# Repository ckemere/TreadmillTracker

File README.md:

# Raspberry pi based interface for a rodent treadmill

  - MSP430 based HW data acquisition "hat"
  - Rotational angle tracking using the CUI AMT 102/3 quadrature encoders
  - 1 kHz master clock for timestamping 8 IO lines

## Setup overview

### PiHat
The custom Raspberry Pi hat contains several useful features.
- **Eight GPIO pins** can be used for either receiving or sending signals.
- **Encoder data (AMT102)** is received through the six pins at the top of the board.  
- **2 kHz master clock (DSC6083)** reliably timestamps input data.
- **Button** ?
- **MSP430 microcontroller** packages and sends serial messages containing timestamped data every 2 ms. Programmed via seven pins at bottom of board.
- **Shield** interfaces with Raspberry Pi pins, including the eight GPIO pins connected to RaspPi GPIO pins.

### Accessories
#### Rotary encoder
The AMT102 sends signals in increments with resolution of 4096 steps/revolution. Thus each pulse signals that the wheel has turned 1/4096 of a revolution. For more details, look at the specs in the data sheet contained in *Firmware*.

#### Lick sensor
The lick sensor sends digital signals to one of the Hat's GPIO pins to indicate a licking event is occurring. More details in lick-sensor repository.

#### Nose-poke sensor
The nose-poke sensor sends digital signals to one of the Hat's GPIO pins to indicate a nose-poke event is occurring.

#### Syringe pump
The syringe pump receives 5V pulses from a GPIO pin on the Hat to dispense liquid rewards. The duration of the pulse determines the volume of reward dispensed (given a syringe diameter and pump speed).

#### Sound card
The sound card converts the digital audio file (.wav) to an analog signal to drive the external speakers. It can either be integrated with the host computer (if using a desktop), or as a shield (if using a Raspberry Pi; the HiFiBerry Amp2, for example, uses built-in drivers in the Raspberry Pi Linux kernel to obtain high-quality I2C digital audio from the GPIO pins, which it converts to an analog signal for speaker input. See [here](https://www.hifiberry.com/build/documentation/configuring-linux-3-18-x/) for more details.)

#### Breakout board
In order to streamline I/O connections between the custom hat and accessories, a custom breakout board shield connects GPIO pins to the rings of 3.5 mm audio jacks. Additionally, the hat Vdd (3.6 V) can be routed to supply voltage to the tips of the audio jacks. With this setup, audio cables can transmit GPIO signal to input and from output devices listed above. For example, audio cables can carry lick and nose-poke sensor digital signals, or send dispense signals to the syringe pumps.

### Host computer
The host computer can either be a Raspberry Pi or a desktop computer. If using a Raspberry Pi, then the custom hat and sound card shield can be stacked on top of one another to form a three-layer, stand-alone device. Otherwise, the host computer is connected to the custom hat via USB, and the native desktop sound card is used to drive the external speakers. In either case, the following components must be installed on the computer.

#### Mixer
The combination of the JACK Audio Connection Kit and minimixer allows for cross-talk between audio sources to function as a software mixer for different audio signals. The JACK daemon runs in the background as a sound server, built on top of the Advanced Linux Sound Architecture (ALSA), for a particular output device (sound card). In a separate process, the minimixer receives different audio feeds in its virtual channels, and controls each sound level of each channel that it feeds into the JACK daemon based on OSC commands it receives. Thus the user has control to dynamically change the output levels of different virtual channels in the minimixer.

#### OSC interface
The mixer, in turn, is interfaced through an OSC package, such `oscpy` in Python, that binds and sends OSC commands to the same port as the mixer. The commands direct the mixer to increase or decrease the gain for each channel in the mixer.

#### Control script
The control script must manage I/O from all the above components, including:
- Processing **behavior input** from the custom hat to determine the current behavior state. The input messages via the serial interface include current time, wheel encoder position, and GPIO values.
- Controlling **audio output** by launching appropriate audio subprocesses (e.g. daemon, mixer) and sending OSC commands to the mixer based on the current behavior state.
- Controlling **behavior output** by sending dispense pulses to the GPIOs associated with syringe pumps based on the current behavior state.

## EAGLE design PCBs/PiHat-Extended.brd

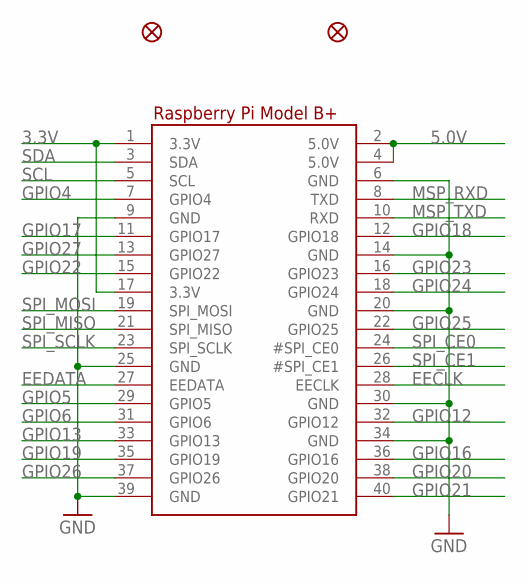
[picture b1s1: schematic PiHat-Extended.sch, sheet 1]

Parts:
FID2, FID3: MICROBUILDER_FIDUCIAL""; MICROBUILDER_FIDUCIAL_1MM
RPI1: MICROBUILDER_RASPBERRYPI_BPLUS_HATNOSLOTS; MICROBUILDER_PI_HAT_NOSLOTS

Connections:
3.3V: RPI1.1 (3.3V), RPI1.17 (3.3V)
5.0V: RPI1.2 (5.0V), RPI1.4 (5.0V); also elsewhere on the board
EECLK: RPI1.28 (EECLK)
EEDATA: RPI1.27 (EEDATA)
GND: RPI1.6 (GND), RPI1.9 (GND), RPI1.14 (GND), RPI1.20 (GND), RPI1.25 (GND), RPI1.30 (GND), RPI1.34 (GND), RPI1.39 (GND); also elsewhere on the board
GPIO4: RPI1.7 (GPIO4)
GPIO5: RPI1.29 (GPIO5); also elsewhere on the board
GPIO6: RPI1.31 (GPIO6); also elsewhere on the board
GPIO12: RPI1.32 (GPIO12)
GPIO13: RPI1.33 (GPIO13)
GPIO16: RPI1.36 (GPIO16); also elsewhere on the board
GPIO17: RPI1.11 (GPIO17); also elsewhere on the board
GPIO18: RPI1.12 (GPIO18)
GPIO19: RPI1.35 (GPIO19)
GPIO20: RPI1.38 (GPIO20)
GPIO21: RPI1.40 (GPIO21)
GPIO22: RPI1.15 (GPIO22); also elsewhere on the board
GPIO23: RPI1.16 (GPIO23); also elsewhere on the board
GPIO24: RPI1.18 (GPIO24); also elsewhere on the board
GPIO25: RPI1.22 (GPIO25); also elsewhere on the board
GPIO26: RPI1.37 (GPIO26); also elsewhere on the board
GPIO27: RPI1.13 (GPIO27); also elsewhere on the board
MSP_RXD: RPI1.8 (TXD); also elsewhere on the board
MSP_TXD: RPI1.10 (RXD); also elsewhere on the board
SCL: RPI1.5 (SCL)
SDA: RPI1.3 (SDA)
SPI_CE0: RPI1.24 (#SPI_CE0)
SPI_CE1: RPI1.26 (#SPI_CE1)
SPI_MISO: RPI1.21 (SPI_MISO)
SPI_MOSI: RPI1.19 (SPI_MOSI)
SPI_SCLK: RPI1.23 (SPI_SCLK)

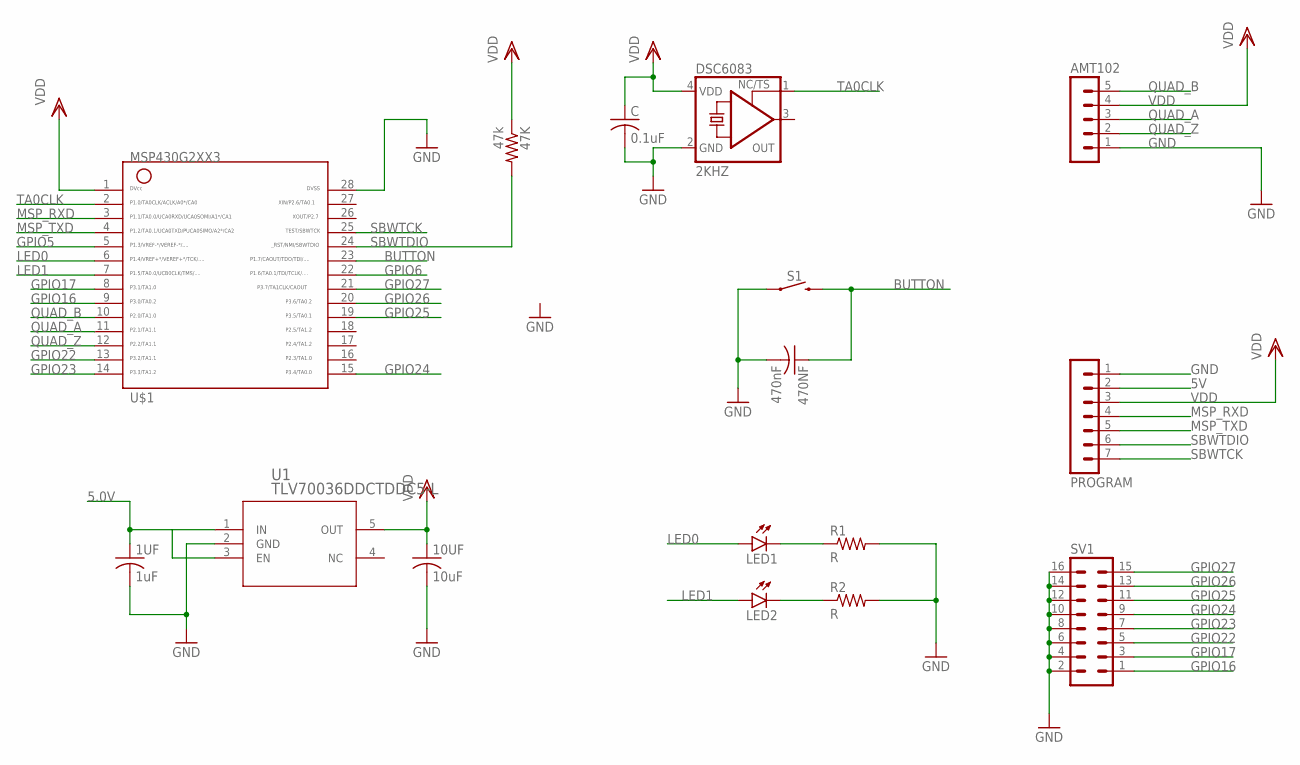
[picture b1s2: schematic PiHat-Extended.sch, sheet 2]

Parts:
1UF: 1uF; C0603
10UF: 10uF; C1206
47K: 47k; R0603
470NF: 470nF; C0603
AMT102: MA05-1
C: 0.1uF; C0603
DSC6083: 2KHZ; 3.2X2.5_KXO-V96
LED1, LED2: LEDCHIPLED_1206; CHIPLED_1206
PROGRAM: MA07-1
R1, R2: R; R0603
S1: MOMENTARY-SWITCH-SPST-PTH-6.0MM; TACTILE_SWITCH_PTH_6.0MM
SV1: MA08-2
U1: TLV70036DDCTDDC5-L; DDC5-L
U$1: MSP430; PW28

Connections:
5.0V: 1UF.1, U1.1 (IN), U1.3 (EN); also elsewhere on the board
5V: PROGRAM.2
BUTTON: 470NF.1, S1.3 (2), U$1.23
GND: 1UF.2, 10UF.2, 470NF.2, AMT102.1, C.2, DSC6083.2 (GND), PROGRAM.1, R1.2, R2.2, S1.1, SV1.2, SV1.4, SV1.6, SV1.8, SV1.10, SV1.12, SV1.14, SV1.16, U1.2 (GND), U$1.28; also elsewhere on the board
GPIO5: U$1.5; also elsewhere on the board
GPIO6: U$1.22; also elsewhere on the board
GPIO16: SV1.1, U$1.9; also elsewhere on the board
GPIO17: SV1.3, U$1.8; also elsewhere on the board
GPIO22: SV1.5, U$1.13; also elsewhere on the board
GPIO23: SV1.7, U$1.14; also elsewhere on the board
GPIO24: SV1.9, U$1.15; also elsewhere on the board
GPIO25: SV1.11, U$1.19; also elsewhere on the board
GPIO26: SV1.13, U$1.20; also elsewhere on the board
GPIO27: SV1.15, U$1.21; also elsewhere on the board
LED0: LED1.A, U$1.6
LED1: LED2.A, U$1.7
MSP_RXD: PROGRAM.4, U$1.3; also elsewhere on the board
MSP_TXD: PROGRAM.5, U$1.4; also elsewhere on the board
unnamed: LED1.C, R1.1
unnamed: LED2.C, R2.1
QUAD_A: AMT102.3, U$1.11
QUAD_B: AMT102.5, U$1.10
QUAD_Z: AMT102.2, U$1.12
SBWTCK: PROGRAM.7, U$1.25
SBWTDIO: 47K.2, PROGRAM.6, U$1.24
TA0CLK: DSC6083.1 (TS), U$1.2
VDD: 10UF.1, 47K.1, AMT102.4, C.1, DSC6083.4 (VDD), PROGRAM.3, U1.5 (OUT), U$1.1; also elsewhere on the board

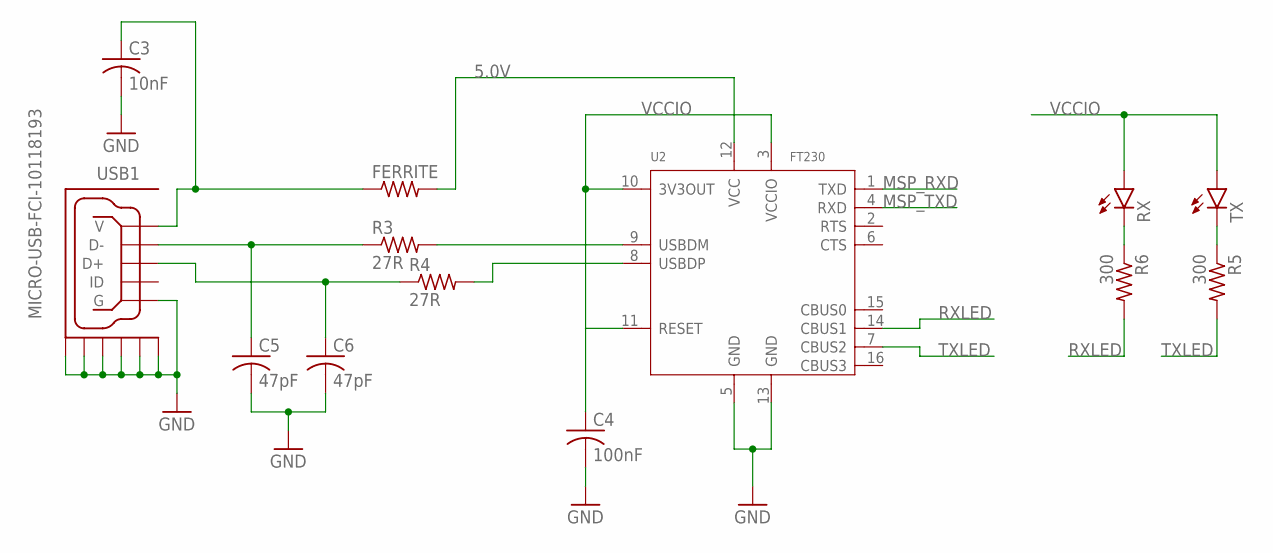
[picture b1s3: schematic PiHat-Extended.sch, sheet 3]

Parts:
C3: 10nF; C0603
C4: 100nF; C0603
C5, C6: 47pF; C0603
FERRITE: R-US_R0805; R0805
R3, R4: 27R; R0603
R5, R6: 300; R0603
RX: LEDCHIPLED_1206; CHIPLED_1206
TX: LEDCHIPLED_1206; CHIPLED_1206
U2: FT230; SSOP16-0.635-5X4MM
USB1: MICRO-USB-FCI-10118193; FCI-10118193-0001LF

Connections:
5.0V: FERRITE.2, U2.12 (VCC); also elsewhere on the board
GND: C3.2, C4.2, C5.2, C6.2, U2.5 (GND), U2.13 (GND), USB1.5 (G), USB1.G1 (GND1), USB1.G2 (GND2), USB1.G3 (GND3), USB1.G4 (GND4), USB1.G5 (GND5), USB1.G6 (GND6); also elsewhere on the board
MSP_RXD: U2.1 (TXD); also elsewhere on the board
MSP_TXD: U2.4 (RXD); also elsewhere on the board
unnamed: C3.1, FERRITE.1, USB1.1 (V)
unnamed: C5.1, R3.1, USB1.2 (D-)
unnamed: R3.2, U2.9 (USBDM)
unnamed: C6.1, R4.1, USB1.3 (D+)
unnamed: R4.2, U2.8 (USBDP)
unnamed: R6.1, RX.C
unnamed: R5.1, TX.C
RXLED: R6.2, U2.14 (CBUS1)
TXLED: R5.2, U2.7 (CBUS2)
VCCIO: C4.1, RX.A, TX.A, U2.3 (VCCIO), U2.10 (3V3OUT), U2.11 (RESET)

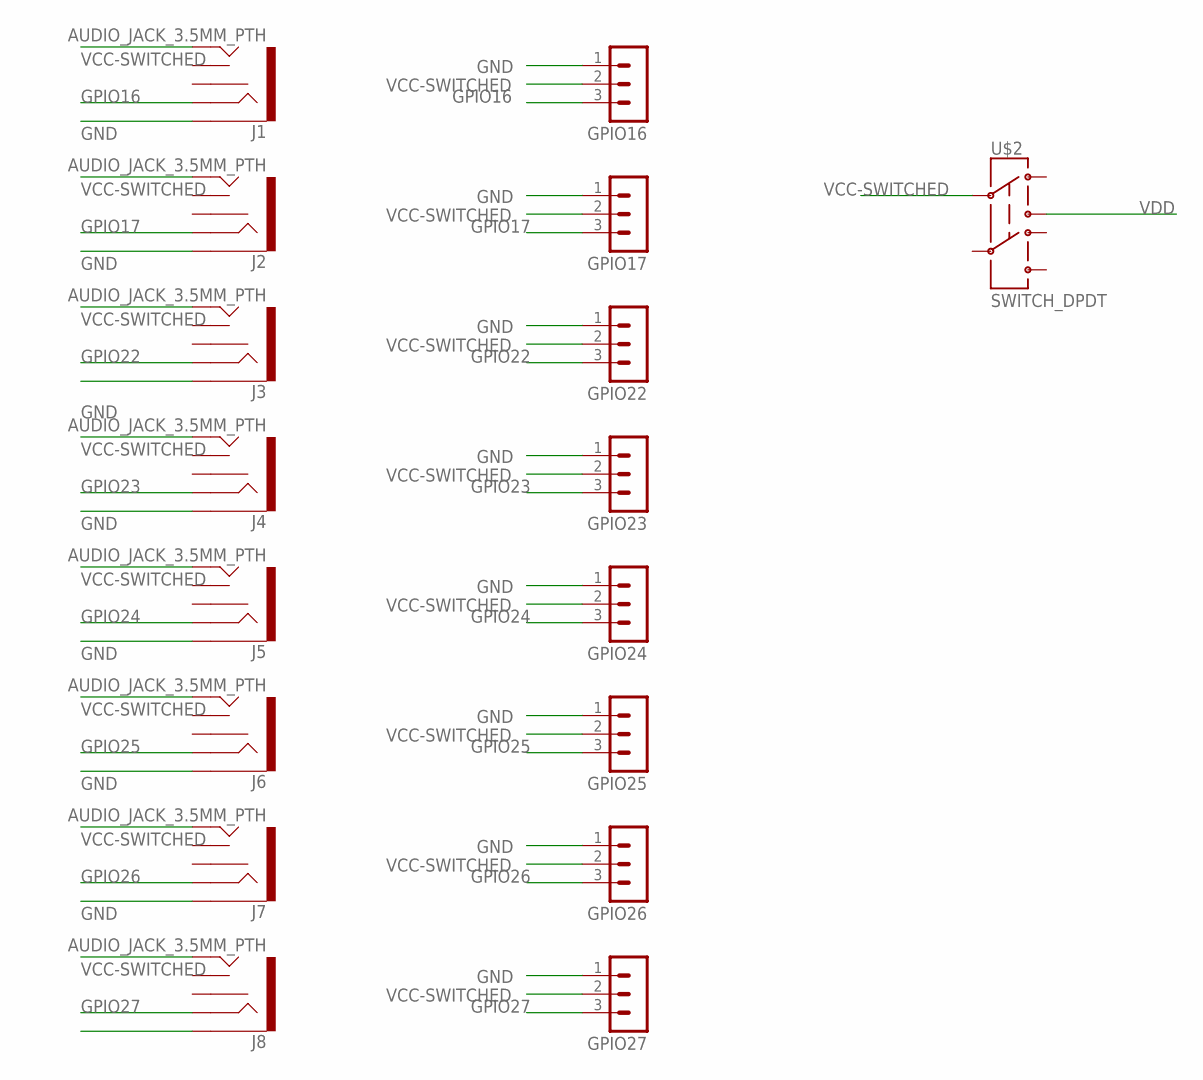
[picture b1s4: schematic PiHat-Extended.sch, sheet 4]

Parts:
GPIO16, GPIO17, GPIO22, GPIO23, GPIO24, GPIO25, GPIO26, GPIO27: MA03-1
J1, J2, J3, J4, J5, J6, J7, J8: AUDIO_JACK_3.5MM_PTH; AUDIO-JACK
U$2: SWITCH_DPDT; JS_DPDT_TH

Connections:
GND: GPIO16.1, GPIO17.1, GPIO22.1, GPIO23.1, GPIO24.1, GPIO25.1, GPIO26.1, GPIO27.1, J1.SLEEVE, J2.SLEEVE, J3.SLEEVE, J4.SLEEVE, J5.SLEEVE, J6.SLEEVE, J7.SLEEVE, J8.SLEEVE; also elsewhere on the board
GPIO16: GPIO16.3, J1.RING; also elsewhere on the board
GPIO17: GPIO17.3, J2.RING; also elsewhere on the board
GPIO22: GPIO22.3, J3.RING; also elsewhere on the board
GPIO23: GPIO23.3, J4.RING; also elsewhere on the board
GPIO24: GPIO24.3, J5.RING; also elsewhere on the board
GPIO25: GPIO25.3, J6.RING; also elsewhere on the board
GPIO26: GPIO26.3, J7.RING; also elsewhere on the board
GPIO27: GPIO27.3, J8.RING; also elsewhere on the board
VCC-SWITCHED: GPIO16.2, GPIO17.2, GPIO22.2, GPIO23.2, GPIO24.2, GPIO25.2, GPIO26.2, GPIO27.2, J1.TIP, J2.TIP, J3.TIP, J4.TIP, J5.TIP, J6.TIP, J7.TIP, J8.TIP, U$2.2
VDD: U$2.3; also elsewhere on the board

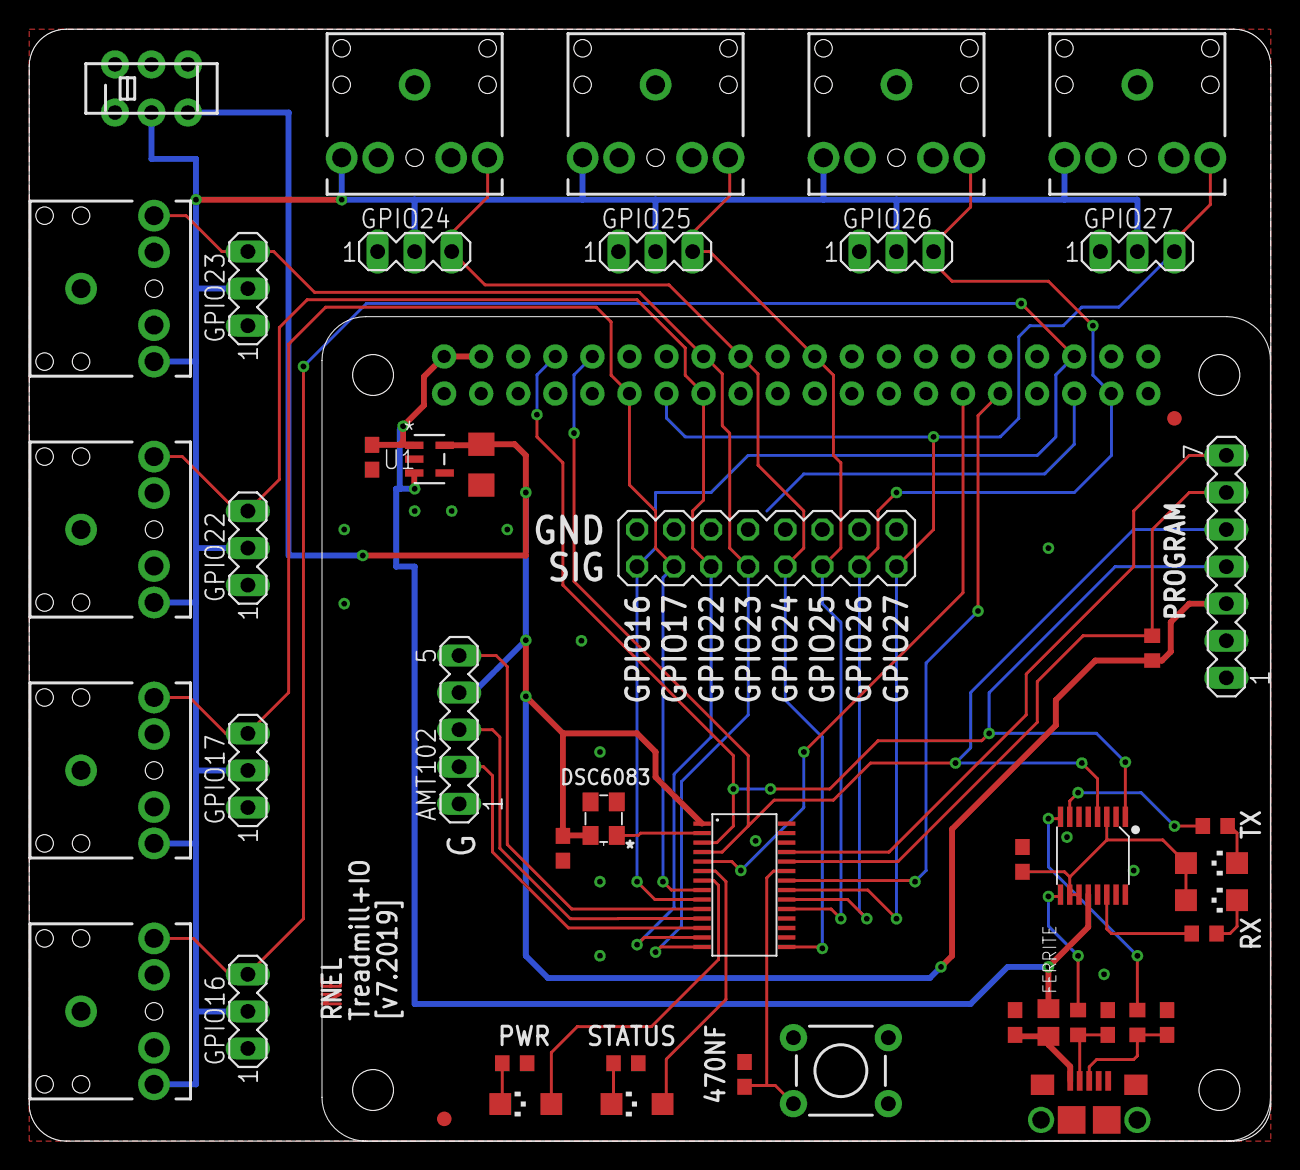
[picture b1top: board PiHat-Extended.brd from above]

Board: 2 copper layers, 85.1 x 76.2 mm, 49 parts (0 on the bottom side), 38 nets.

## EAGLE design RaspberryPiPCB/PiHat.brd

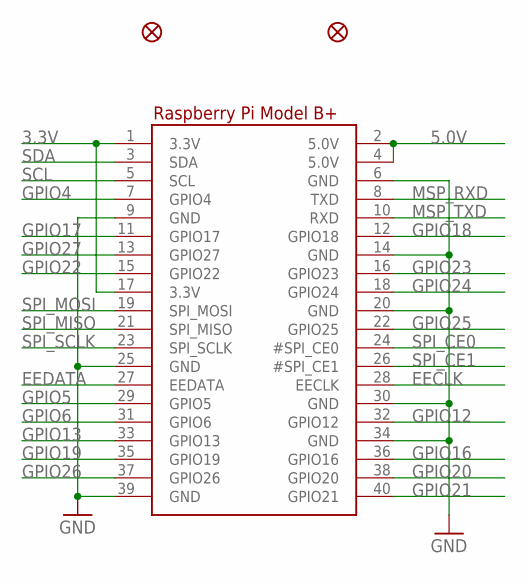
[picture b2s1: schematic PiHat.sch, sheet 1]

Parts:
FID2, FID3: FIDUCIAL""; FIDUCIAL_1MM
RPI1: RASPBERRYPI_BPLUS_HATNOSLOTS; PI_HAT_NOSLOTS

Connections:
3.3V: RPI1.1 (3.3V), RPI1.17 (3.3V)
5.0V: RPI1.2 (5.0V), RPI1.4 (5.0V); also elsewhere on the board
EECLK: RPI1.28 (EECLK)
EEDATA: RPI1.27 (EEDATA)
GND: RPI1.6 (GND), RPI1.9 (GND), RPI1.14 (GND), RPI1.20 (GND), RPI1.25 (GND), RPI1.30 (GND), RPI1.34 (GND), RPI1.39 (GND); also elsewhere on the board
GPIO4: RPI1.7 (GPIO4)
GPIO5: RPI1.29 (GPIO5); also elsewhere on the board
GPIO6: RPI1.31 (GPIO6); also elsewhere on the board
GPIO12: RPI1.32 (GPIO12)
GPIO13: RPI1.33 (GPIO13)
GPIO16: RPI1.36 (GPIO16); also elsewhere on the board
GPIO17: RPI1.11 (GPIO17); also elsewhere on the board
GPIO18: RPI1.12 (GPIO18); also elsewhere on the board
GPIO19: RPI1.35 (GPIO19); also elsewhere on the board
GPIO20: RPI1.38 (GPIO20)
GPIO21: RPI1.40 (GPIO21)
GPIO22: RPI1.15 (GPIO22)
GPIO23: RPI1.16 (GPIO23)
GPIO24: RPI1.18 (GPIO24); also elsewhere on the board
GPIO25: RPI1.22 (GPIO25); also elsewhere on the board
GPIO26: RPI1.37 (GPIO26); also elsewhere on the board
GPIO27: RPI1.13 (GPIO27); also elsewhere on the board
MSP_RXD: RPI1.8 (TXD); also elsewhere on the board
MSP_TXD: RPI1.10 (RXD); also elsewhere on the board
SCL: RPI1.5 (SCL)
SDA: RPI1.3 (SDA)
SPI_CE0: RPI1.24 (#SPI_CE0)
SPI_CE1: RPI1.26 (#SPI_CE1)
SPI_MISO: RPI1.21 (SPI_MISO)
SPI_MOSI: RPI1.19 (SPI_MOSI)
SPI_SCLK: RPI1.23 (SPI_SCLK)

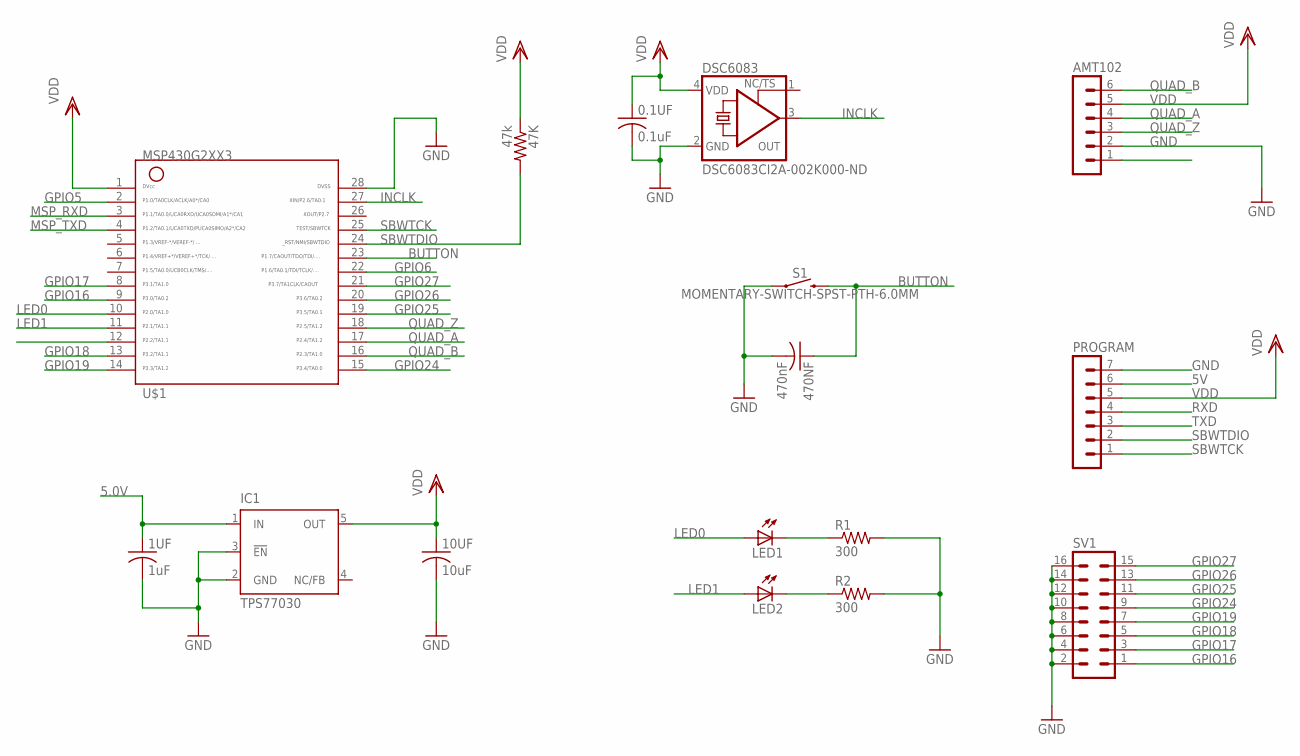
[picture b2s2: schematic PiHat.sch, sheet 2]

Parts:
0.1UF: 0.1uF; C0603
1UF: 1uF; C0603
10UF: 10uF; C1206
47K: 47k; R0603
470NF: 470nF; C0603
AMT102: MA06-1
DSC6083: DSC6083CI2A-002K000-ND; 3.2X2.5_KXO-V96
IC1: TPS77030; SOT23-DBV
LED1, LED2: LEDCHIPLED_1206; CHIPLED_1206
PROGRAM: MA07-1
R1, R2: 300; R0603
S1: MOMENTARY-SWITCH-SPST-PTH-6.0MM; TACTILE_SWITCH_PTH_6.0MM
SV1: MA08-2
U$1: G2XX3---PW28; PW28

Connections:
5.0V: 1UF.1, IC1.1 (IN); also elsewhere on the board
5V: PROGRAM.6
BUTTON: 470NF.1, S1.3 (2), U$1.23
GND: 0.1UF.2, 1UF.2, 10UF.2, 470NF.2, AMT102.2, DSC6083.2 (GND), IC1.2 (GND), IC1.3 (!EN), PROGRAM.7, R1.2, R2.2, S1.1, SV1.2, SV1.4, SV1.6, SV1.8, SV1.10, SV1.12, SV1.14, SV1.16, U$1.28; also elsewhere on the board
GPIO5: U$1.2; also elsewhere on the board
GPIO6: U$1.22; also elsewhere on the board
GPIO16: SV1.1, U$1.9; also elsewhere on the board
GPIO17: SV1.3, U$1.8; also elsewhere on the board
GPIO18: SV1.5, U$1.13; also elsewhere on the board
GPIO19: SV1.7, U$1.14; also elsewhere on the board
GPIO24: SV1.9, U$1.15; also elsewhere on the board
GPIO25: SV1.11, U$1.19; also elsewhere on the board
GPIO26: SV1.13, U$1.20; also elsewhere on the board
GPIO27: SV1.15, U$1.21; also elsewhere on the board
INCLK: DSC6083.3 (OUT), U$1.27
LED0: LED1.A, U$1.10
LED1: LED2.A, U$1.11
MSP_RXD: U$1.3; also elsewhere on the board
MSP_TXD: U$1.4; also elsewhere on the board
unnamed: LED1.C, R1.1
unnamed: LED2.C, R2.1
QUAD_A: AMT102.4, U$1.17
QUAD_B: AMT102.6, U$1.16
QUAD_Z: AMT102.3, U$1.18
RXD: PROGRAM.4
SBWTCK: PROGRAM.1, U$1.25
SBWTDIO: 47K.2, PROGRAM.2, U$1.24
TXD: PROGRAM.3
VDD: 0.1UF.1, 10UF.1, 47K.1, AMT102.5, DSC6083.4 (VDD), IC1.5 (OUT), PROGRAM.5, U$1.1

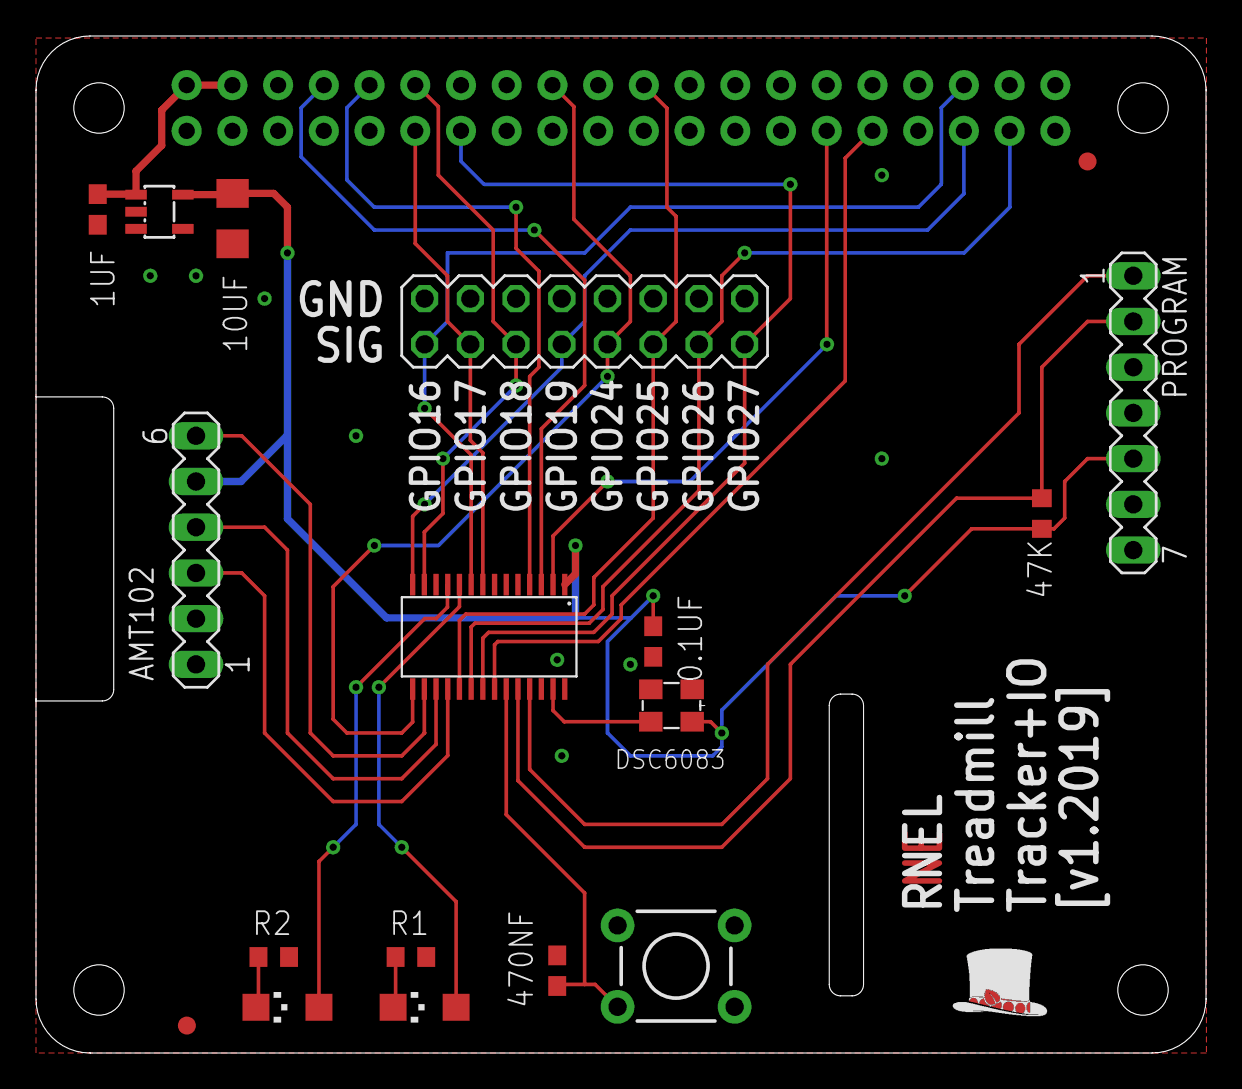
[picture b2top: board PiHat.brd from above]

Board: 2 copper layers, 65.0 x 56.5 mm, 20 parts (0 on the bottom side), 27 nets.

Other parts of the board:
U$2: PIHATLOGO

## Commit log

2019-01-01 First commit of firmware and EAGLE cad design
2019-01-01 created license file
2019-01-02 Final design for manufacturing
2019-01-03 Added 3D design files directory and first end caps for PVC axels
2019-01-04 Updated directory names and added EAGLE Cad gitignore
2019-01-11 Added more treadmill parts
2019-01-17 Updated board after debugging first revision
2019-01-17 Updated firmware to match PCB
2019-01-22 Added 3D printed standoffs for Pi Hat PCB
2019-01-25 Added T Slot Joiner piece
2019-03-01 Updated height
2019-03-22 Added 80-20 sliding bearing mounts for waterjet cutting
2019-03-25 Modified firmware (timing + binary UART data). Added PDF of schematic.
2019-03-25 Updated PDF
2019-03-25 Added Energia ino file for firmware
2019-03-25 Added simple Python script for testing UART comms
2019-03-25 Added manufacturing files from first run
2019-03-26 Updated code some more trying to get 2kHz clock to work
2019-03-30 Fixed errors and added a FT230 USB/UART Interface to PCB
2019-03-30 Updated design files
2019-03-30 Updated interface PCB to have proper silkscreen and added manufacturing files
2019-04-17 Updated firmware code to properly use 2kHz source for newest PCBs. Fixed bug in UART initialization that overwrote P1SEL!
2019-04-19 Updated firmware to make time ISRs use assembly.
2019-04-22 Created entire Quadrature ISR in assembly. Also changed encoder counter to 16 bit
2019-04-23 Split quadrature decoding isr code into it's own files; rewrote UART word-send in assembly; Updated Python test reader for FTDI interfaec
2019-04-23 Added OMAX illustrator files for treadmill arms and 3D printed adaptors for axel and Encoder mount
2019-04-29 Fixed bug where Quadrature header include guard was labeled UART_H by mistake. Added GPIO output from Port 3. Added receive interrupt which writes the received byte to the output port (we really shou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
2019-04-29 Updated mounting hole positions on encoder mount
2019-04-29 Updated designs for lighter weight acrylic axels
2019-05-08 Updated client side code to synchronize when a large block of data might be sent that makes serial buffer off-sync of 9 byte packets
2019-05-16 Figured out that latency timer affects data transfer rate. Figured out how to update it (documented in ClientSide/README.md) with udev rule. Updated data transmission rate to 2 ms, which seems to wor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
2019-05-20 Added some notes about testing sound control of stimuli
2019-05-20 Added some example python code for controlling OSC messages
2019-05-23 Fixed two bugs in design where there were vias that were shorting
2019-05-25 Added notes for Raspberry Pi and Python latency test code
2019-05-25 Added more notes for Raspberry Pi
2019-05-25 Added more notes about the Raspberry Pi interface
2019-05-29 Added code to generate simple wave-file player for jack audio originally from the sndfile-tools library, as well as python code to generate a simple single-tone wave file
2019-05-29 Updated notes for Audio latency tests
2019-05-29 Forgot to mention oscpy in notes. Fixed
2019-05-31 Added FTDI latency timer instructions for windows.
2019-05-31 Added python script to log data to a csv file.
2019-06-06 Added link to Ubuntu raspi arm64 image
2019-06-06 Added a link to the ubuntu raspi arm64 image
2019-06-07 Added instructions for getting the Raspberry Pi up and running first.
2019-06-09 Moved testing files to TestDev directory and added argument parsing to LogData.py
2019-06-09 Updated arguments for LogData
2019-06-09 Finished moving into new directory
2019-06-10 Added raspberry pi closed loop testing script
2019-06-12 Added test of closed loop wheel control of sound
2019-06-12 Updated instructions for starting jackminimix to include -p 12345 option, defaulting the OSC port to 12345
2019-06-22 (1) Changed firmware to make all GPIOs input. (2) Added command line args to ReadUART.py
2019-06-22 Added more files for treadmill and wheel mounting
2019-06-22 Added datasheet for AMT10 rotational sensor from CUI
2019-06-25 Added Unwrapped Encoder data (32 bit) and updated Python code. Rearchitected for GCC toolchain. Added Makefiale.
2019-06-25 Removed debugging hint which started Unwrapped phase at 100000. Note that we still have PULL DOWN resistors enabled.
2019-06-25 Removed PULL UP resistors.
2019-06-26 Changed format for UnwrappedEncoder data from unsigned long to long
2019-06-26 Changed program name to 'treadmill.elf' in Makefile and added helpful comments about debugging with gdb
2019-06-26 Added more helpful comments about compiler flags for debugging with gdb
2019-06-26 Improved tracking of index pin
2019-06-26 Changed naming of Quadrature files to be lowercase (quadrature) to match other files
2019-06-26 Changed eptr to unsigned char to get rid of warning
2019-07-02 notebook to test different auditory stimuli
2019-07-03 added gitignore for ClientSide
2019-07-03 added white noise filter for pink noise
2019-07-03 Created a prototype linear track script.
2019-07-03 Raspberry Pi-related updates to Linear Track code
2019-07-04 Added missing quote for generating a password in python.
2019-07-04 Add links to github for jackminimix and sndfile-tools
2019-07-04 Fixed links from last commit.
2019-07-04 Add dependences to Audio install instructions
2019-07-05 Added stimulus generation python code and notebook as well as longer versions of stimuli
2019-07-05 Updated LinearTrack script with tone wave file
2019-07-06 Fixed Linear Track script bug that was causing issues
2019-07-06 Double checked and cleaned up headpost designs
2019-07-06 Updated link to Ghanbari paper
2019-07-08 Added standard FTDI udev rule for FT230X to udev rules file
2019-07-08 fixed tone frequency and cosine gating bugs
2019-07-08 added comments
2019-07-08 Split linear track code into two - StartAudio and LinearTrack
2019-07-08 Updated comments in LinearTrack code to reflect need for serial initialization to immediately proceed main loop.
2019-07-09 Updated Firmware and LinearTrack code to also include controlling output
2019-07-09 Updated firmware so that the top 3 bits are outputs
2019-07-10 added learning comments to readme and firmware
2019-07-10 added msp430 instruction manual for reference
2019-07-11 restructured directory tree
2019-07-11 placeholder for training task
2019-07-11 added default task parameters
2019-07-11 moved raspberry pi setup to separate folder
2019-07-11 added more installation instructions
2019-07-11 added settings file for task
2019-07-11 moved auditory stimuli to separate directory
2019-07-11 added basic training task for one animal
2019-07-11 ignore vscode files
2019-07-11 bug fixes (especially serial transmission with integer)
2019-07-11 directed log to output directory
2019-07-12 moved more scripts to test suite
2019-07-12 renamed to be consistent with repo
2019-07-12 Update description of udev rule and groups for FTDI interface
2019-07-12 Added note about audio group to Audio instructions.
2019-07-17 added mouse ID to default settings files
2019-07-20 Updated organization of 3D printed wheel and treadmill parts
2019-07-20 Added positioner posts to treadmill side pieces
2019-07-20 More cleanups of 3D printed parts
2019-07-20 Updated Headplate files (should double check this)
2019-07-26 padded time to poke entry/exit
2019-07-27 add head fix training tasks
2019-07-27 added head fix tasks
2019-07-29 Added treadmill belt wheel design and old paper about crowning
2019-07-29 Added laser cut acrylc versions of treadmill parts
2019-08-02 added volume change with distance
2019-08-06 added output side argument
2019-08-07 fixed mask encoding for most significant bit
2019-08-07 updated version description for earlier version
2019-08-07 updated for new firmware
2019-08-07 add different frequencies of tones
2019-08-08 ignored additional config files
2019-08-09 added notebook to test reward decay functions
2019-08-09 fixed mistake in derivatives
2019-08-10 added minor details to jack and minimix usage
2019-08-18 Added new Teensy-based hardware breakout board
2019-08-20 small clarification of R_0
2019-08-20 added exponentially decaying reward function
2019-08-20 minor bug fix
2019-08-20 added reward decay parameters
2019-08-20 reorganized audio control to json file
2019-08-20 minor bug fixes
2019-08-21 changed naming of saved files
2019-08-21 fixed re-entry bug
2019-08-30 added guvcview interface for recording video
2019-08-30 recalibrated tone sound level
2019-08-30 added comments/resources
2019-09-03 clarified camera output vs. video codec
2019-09-03 switched to monotonic clock
2019-09-03 updated timestamp to match miniscope monotonic time
2019-09-04 added column labels for data log file
2019-09-04 clarified video format vs codec for camera setting
2019-09-04 added max trigger count for operant task
2019-09-05 Added a Teensy version of the Firmware.
2019-09-06 re-configured sound and pump logic
2019-09-06 cleaned up files and directories
2019-09-06 added missing file
2019-09-11 added script to prime reward wells
2019-11-14 updated tone cloud stimuli; saved sound params
2019-11-19 added info about JACK setup
2019-11-19 added some useful links
2019-12-05 First commit of new auditory VR framework. No sound yet, but created simulator and visualization
2019-12-09 Working track simulator with Classical Conditioning reward
2019-12-12 Fixed bug with sound zone width
2019-12-13 Updated task possibilities to include Operant reward
2019-12-15 Added treadmill belt wheel designs for 3D extrusion printing
2019-12-16 Added Kinemouse wheel files
2019-12-23 Updated to log data and also cover physical tracks
2020-01-11 Lots of 3D design changes
2020-02-07 Updated render track to work in terms of length rather than circular units
2020-02-07 Edited GenerateAudio to make all files 48 kHz
2020-02-08 Changes made for testing latency
2020-02-08 Made changes and added a latency test script and config yaml file
2020-02-08 Added a comment which describes how to start the jack daemon
2020-02-25 serial and camera interfaces
2020-02-25 test webcam sync based on system timestamps
2020-03-18 Added a new head plate holder design with two pieces that reach from behind as well as a visualization of the whole assembly. Updated holders so there are standard and 4.72 mm versions (compatible wi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
2020-03-20 initial commit for two-speaker task
2020-03-20 test roundtrip latency on JACK server
2020-04-01 notebook to test roundtrip audio latency on JACK
2020-04-10 added more tones
2020-08-07 Uploaded PDF versions of design files
2020-08-27 Updated LED holder so that fatter hdmi or usb cables fit

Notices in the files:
parts and their libraries:
SparkFun-Switches: Licensing: Creative Commons ShareAlike 4.0 International - https://creativecommons.org/licenses/by-sa/4.0
crystal-geyer_V1_0: Copyright: Geyer-Electronic
